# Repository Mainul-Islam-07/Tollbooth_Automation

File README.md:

#  🚧 Tollbooth_Automation
## ℹ️ Overview
Developed an automated tollbooth system capable of managing vehicle access efficiently, securely, and intelligently using a state machine–based control architecture.
The core logic is modeled as a finite state machine, enabling the system to transition between different operational modes depending on real-time triggers like camera input, payment status, vehicle movement, or override commands.
## 🌟 Highlights

### Microcontroller 💻
STM32F103C8t6 is used as the microcontroller.

### Ethernet Communication 🌐
Wiznet W5500 is used for Ethernet communication with the computer.

### UART Communication 🔄
Two UART communication interfaces (One of them is for debugging).

## ⚙️ Features 
### Vehicle Detection (Entry) 🚗
Detection of an approaching vehicle using inductive loop coils installed on the entry lane.

### Automated Boom Barrier Control 🚧
The boom barrier is raised or lowered based on toll payment status and vehicle position, ensuring only authorized passage.

### Vehicle Detection (Exit) 🚙
Detection of a car leaving the toll area is also handled via loop coils on the exit side.

### Car Exit Confirmation via IR Sensor 🌟
An IR sensor provides an additional check to confirm that the car has left the toll zone properly.

### Siren Control for Violations 🚨
A siren is triggered in case of illegal car passage (e.g., unpaid exit) and turned off after resolution or proper payment.

### TCU Breach Detection 🔒
The system monitors for unauthorized access or tampering with the Toll Controller Unit (TCU) and issues alerts on breach.

### Lane Operation Light Control 💡
The system manages lane indicator lights, guiding operators and drivers based on system state (e.g., red/green lights for status).

### Overhead Light Control 🌙
Overhead lighting at the booth is automatically controlled depending on operational mode or time of day.

### Additional Device Control (x3) ⚙️
Provision to control three additional AC or DC devices, configurable for future expansion (e.g., fan, display board, heater).

### PC Power Control (Upcoming) 💻
Planned feature to automatically turn the PC on/off based on toll activity or scheduled requirements. (Not yet implemented)

### Event Logging with External RTC (Upcoming) 🕰️
Future capability to log system events and state changes using a Real-Time Clock (RTC) module for time-stamped data. (Not yet implemented)

## Other Important aspects:

### Wiznet Interrupt-Based Communications 

### UART DMA Interrupt-Based Communication 

### Optocoupler-Based Input/Output for Isolation

### Encrypted Communication 🔐 (Not implemented yet)

## LED Board Config

## 🔁State Machine

## 🔧 Input/Output Circuit Diagram (Not Updated - Need Fix)

## PCB Sample Image

## Proteus Simulation Sample (Not Updated - Need Fix)

# ICPS Header Connection between PCBs

# Relay Board Pinout

## ⬇️ Installation

Download and Install STM32CubeIDE from https://www.st.com/en/development-tools/stm32cubeide.html

Download and Install Hercules from https://www.hw-group.com/software/hercules-setup-utility

Download and Install Serial Debugger Assistant from https://apps.microsoft.com/detail/9nblggh43hdm?hl=en-US&gl=US

## Setup

1) Download the zip or fork and then clone to a local directory
2) Import the folder as a project in STM32CubeIde
3) Plug the mcu using st-link v2 where,

| MCU Pin (90° Bent)     | Corresponding Pin on ST Link V2 |
|------------------------|-------------------|
| 3V3 (90 Degree Bent)   | 3V3               |
| GND (90 Degree Bent)   | GND               |
| SWDIO (90 Degree Bent) | SWDIO             |
| SCLK (90 Degree Bent)  | SCLK              |

Like this,

Then, plug the usb type A of ST-LINK V2 to Computer.

4) Press "Run" in the CubeIDE. Done!

# PCB PROBLEMS / SOLUTIONS / CONCERNS

2nd Iteration PCB is not finalized yet.

## TOLL CONTROLLER UNIT

1) SCLK And RST Connection from W5500 to MCU is manually swapped using wires. It should be fixed in next PCB design Iteration.
2) TX and RX connection from both UARTs is manually swapped using wires. The ususal way is UART TX > MCU TX and UART RX > MCU RX. To be fixed in the nextIteration.

3) Since less current flow at Input, 1k ohm resistors attached at all of the 4 inputs in replaced by wire (shorting). Now the optocoupler responses any voltage from 6V. To be fixed in next iteration.
4) Voltage divider resistors are changed from 22k and 33k to 470 and 1k ohm for all inputs. It provides proper input to the mcu pins. To be fixed in next iteration.

5) All 470 ohm connected from MCU to Relay signal input side is manually shorted. This is done for proper signal sending. To be fixed in next iteration.
6) Voltage divider resistors are changed from 22k and 33k to 33k and 100k for All UART RX. To be fixed in the next iteration.

8) w5500 needs to be powered using a regulator from 5V to 3.3V. To be Fixed in next iteration.

## RELAY BOARD

1) The resistor after 470 ohm should not be used. It should be kept open. To be fixed in the next iteration.
2) A pullup of 10k is given from 12 volt to base of bc557 in such a way that it can be made 0V / 12V when needed. To be fixed in the next iteration.

3) Pulldown resistor is given of 100k ohm resistors.

## LED BOARD

1) 1k ohm is connected to every signal end of mosfet used for powering RGB LED. Otherwise biasing issues emerge. To be fixed in the next iteration.

2) Led that are powered by mcu directly should be equiped with less value resistor, lets say 100ohm. Applicable for Camera_Trigger, Payment and Ping LEDs.

# CODE PROBLEMS / SOLUTIONS / CONCERNS

1) Individual Flags for sensor update should be implemented in next iteration. 
2) CMD_NO_COMMAND should replace CMD_RESET as default outcome from processcommand.

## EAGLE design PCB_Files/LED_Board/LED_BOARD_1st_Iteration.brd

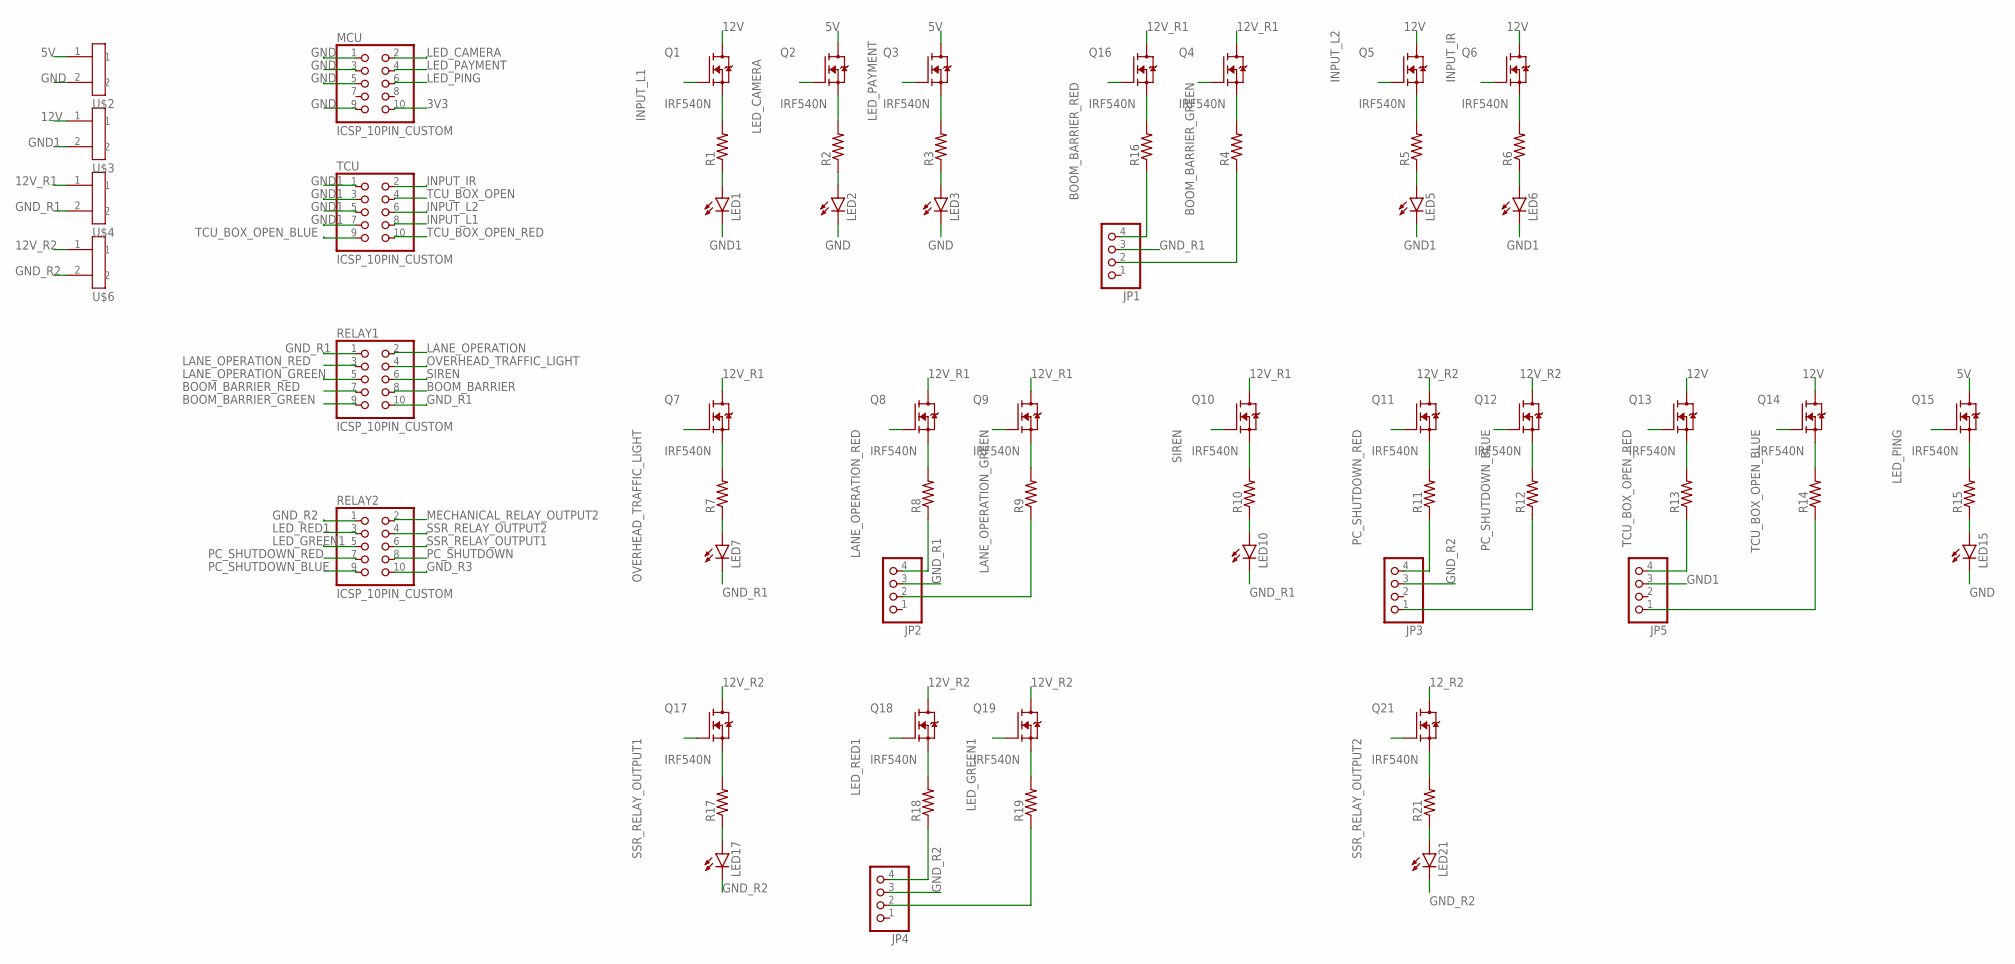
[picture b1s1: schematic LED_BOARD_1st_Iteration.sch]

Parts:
JP1, JP2, JP3, JP4, JP5: PINHD-1X4; 1X04
LED1, LED2, LED3, LED5, LED6, LED7, LED10, LED15, LED17, LED21: LED
MCU: ICSP_10PIN_CUSTOM
Q1, Q2, Q3, Q4, Q5, Q6, Q7, Q8, Q9, Q10, Q11, Q12, Q13, Q14, Q15, Q16, Q17, Q18, Q19, Q21: IRF540N; TO254P1054X469X1930-3
R1, R2, R3, R4, R5, R6, R7, R8, R9, R10, R11, R12, R13, R14, R15, R16, R17, R18, R19, R21: RESISTOR
RELAY1, RELAY2: ICSP_10PIN_CUSTOM
TCU: ICSP_10PIN_CUSTOM
U$2, U$3, U$4, U$6: GREEN_PLUG_90_2

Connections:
3V3: MCU.10
5V: Q2.2 (D), Q3.2 (D), Q15.2 (D), U$2.1
12V: Q1.2 (D), Q5.2 (D), Q6.2 (D), Q13.2 (D), Q14.2 (D), U$3.1
12V_R1: Q4.2 (D), Q7.2 (D), Q8.2 (D), Q9.2 (D), Q10.2 (D), Q16.2 (D), U$4.1
12V_R2: Q11.2 (D), Q12.2 (D), Q17.2 (D), Q18.2 (D), Q19.2 (D), U$6.1
12_R2: Q21.2 (D)
BOOM_BARRIER: RELAY1.8
BOOM_BARRIER_GREEN: Q4.1 (G), RELAY1.9
BOOM_BARRIER_RED: Q16.1 (G), RELAY1.7
GND: LED2.K (C), LED3.K (C), LED15.K (C), MCU.1, MCU.3, MCU.5, MCU.9, U$2.2
GND1: JP5.3, LED1.K (C), LED5.K (C), LED6.K (C), TCU.1, TCU.3, TCU.5, TCU.7, U$3.2
GND_R1: JP1.3, JP2.3, LED7.K (C), LED10.K (C), RELAY1.1, RELAY1.10, U$4.2
GND_R2: JP3.3, JP4.3, LED17.K (C), LED21.K (C), RELAY2.1, U$6.2
GND_R3: RELAY2.10
INPUT_IR: Q6.1 (G), TCU.2
INPUT_L1: Q1.1 (G), TCU.8
INPUT_L2: Q5.1 (G), TCU.6
LANE_OPERATION: RELAY1.2
LANE_OPERATION_GREEN: Q9.1 (G), RELAY1.5
LANE_OPERATION_RED: Q8.1 (G), RELAY1.3
LED_CAMERA: MCU.2, Q2.1 (G)
LED_GREEN1: Q19.1 (G), RELAY2.5
LED_PAYMENT: MCU.4, Q3.1 (G)
LED_PING: MCU.6, Q15.1 (G)
LED_RED1: Q18.1 (G), RELAY2.3
MECHANICAL_RELAY_OUTPUT2: RELAY2.2
unnamed: Q1.3 (S), R1.2
unnamed: LED1.A, R1.1
unnamed: JP1.4, R16.1
unnamed: JP1.2, R4.1
unnamed: JP2.4, R8.1
unnamed: Q2.3 (S), R2.2
unnamed: LED2.A, R2.1
unnamed: JP2.2, R9.1
unnamed: JP5.4, R13.1
unnamed: JP3.4, R11.1
unnamed: Q3.3 (S), R3.2
unnamed: LED3.A, R3.1
unnamed: JP3.1, R12.1
unnamed: JP5.1, R14.1
unnamed: Q4.3 (S), R4.2
unnamed: Q5.3 (S), R5.2
unnamed: LED5.A, R5.1
unnamed: Q6.3 (S), R6.2
unnamed: LED6.A, R6.1
unnamed: Q7.3 (S), R7.2
unnamed: LED7.A, R7.1
unnamed: Q8.3 (S), R8.2
unnamed: Q9.3 (S), R9.2
unnamed: Q10.3 (S), R10.2
unnamed: LED10.A, R10.1
unnamed: Q11.3 (S), R11.2
unnamed: Q12.3 (S), R12.2
unnamed: Q13.3 (S), R13.2
unnamed: Q14.3 (S), R14.2
unnamed: Q15.3 (S), R15.2
unnamed: LED15.A, R15.1
unnamed: Q16.3 (S), R16.2
unnamed: Q17.3 (S), R17.2
unnamed: LED17.A, R17.1
unnamed: Q18.3 (S), R18.2
unnamed: JP4.4, R18.1
unnamed: Q19.3 (S), R19.2
unnamed: JP4.2, R19.1
unnamed: Q21.3 (S), R21.2
unnamed: LED21.A, R21.1
OVERHEAD_TRAFFIC_LIGHT: Q7.1 (G), RELAY1.4
PC_SHUTDOWN: RELAY2.8
PC_SHUTDOWN_BLUE: Q12.1 (G), RELAY2.9
PC_SHUTDOWN_RED: Q11.1 (G), RELAY2.7
SIREN: Q10.1 (G), RELAY1.6
SSR_RELAY_OUTPUT1: Q17.1 (G), RELAY2.6
SSR_RELAY_OUTPUT2: Q21.1 (G), RELAY2.4
TCU_BOX_OPEN: TCU.4
TCU_BOX_OPEN_BLUE: Q14.1 (G), TCU.9
TCU_BOX_OPEN_RED: Q13.1 (G), TCU.10

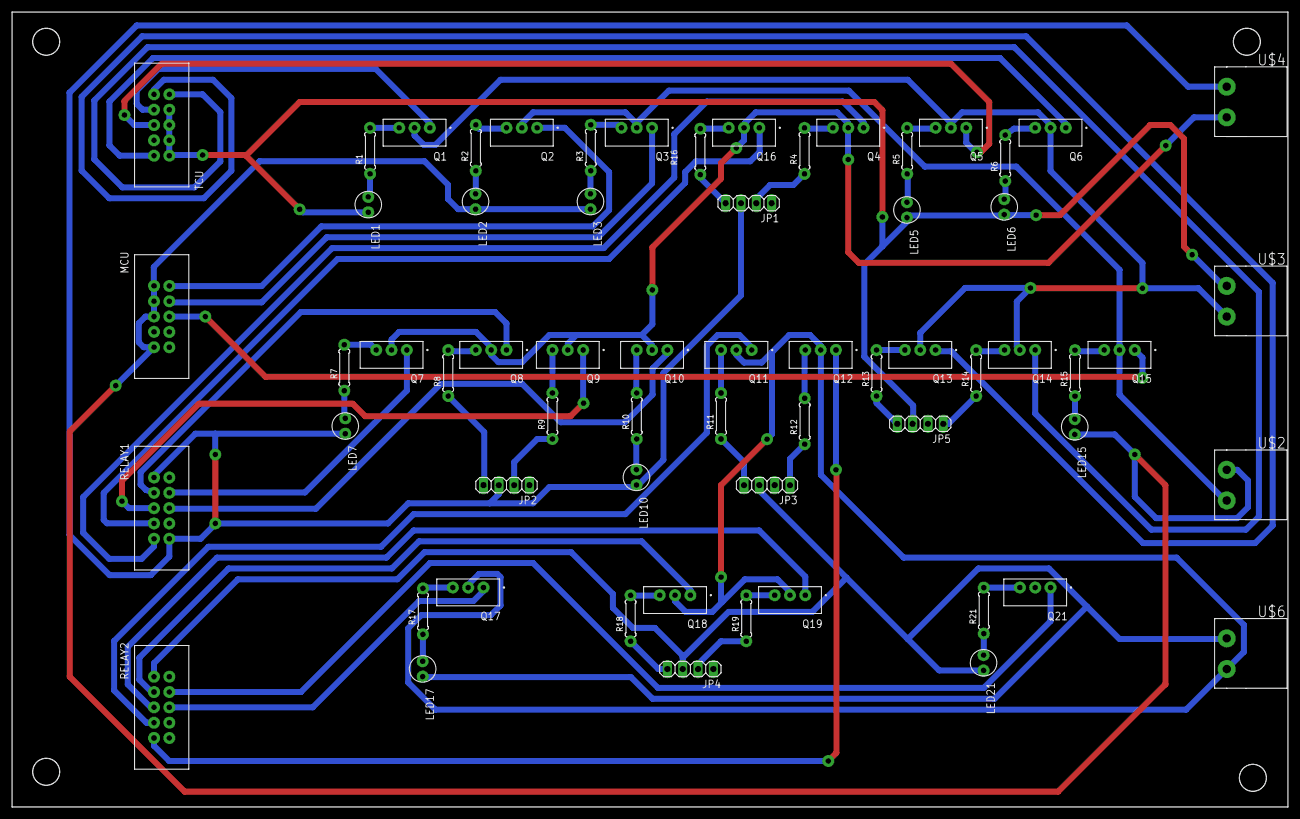
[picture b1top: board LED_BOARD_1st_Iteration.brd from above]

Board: 2 copper layers, 211.3 x 131.6 mm, 63 parts (0 on the bottom side), 68 nets.

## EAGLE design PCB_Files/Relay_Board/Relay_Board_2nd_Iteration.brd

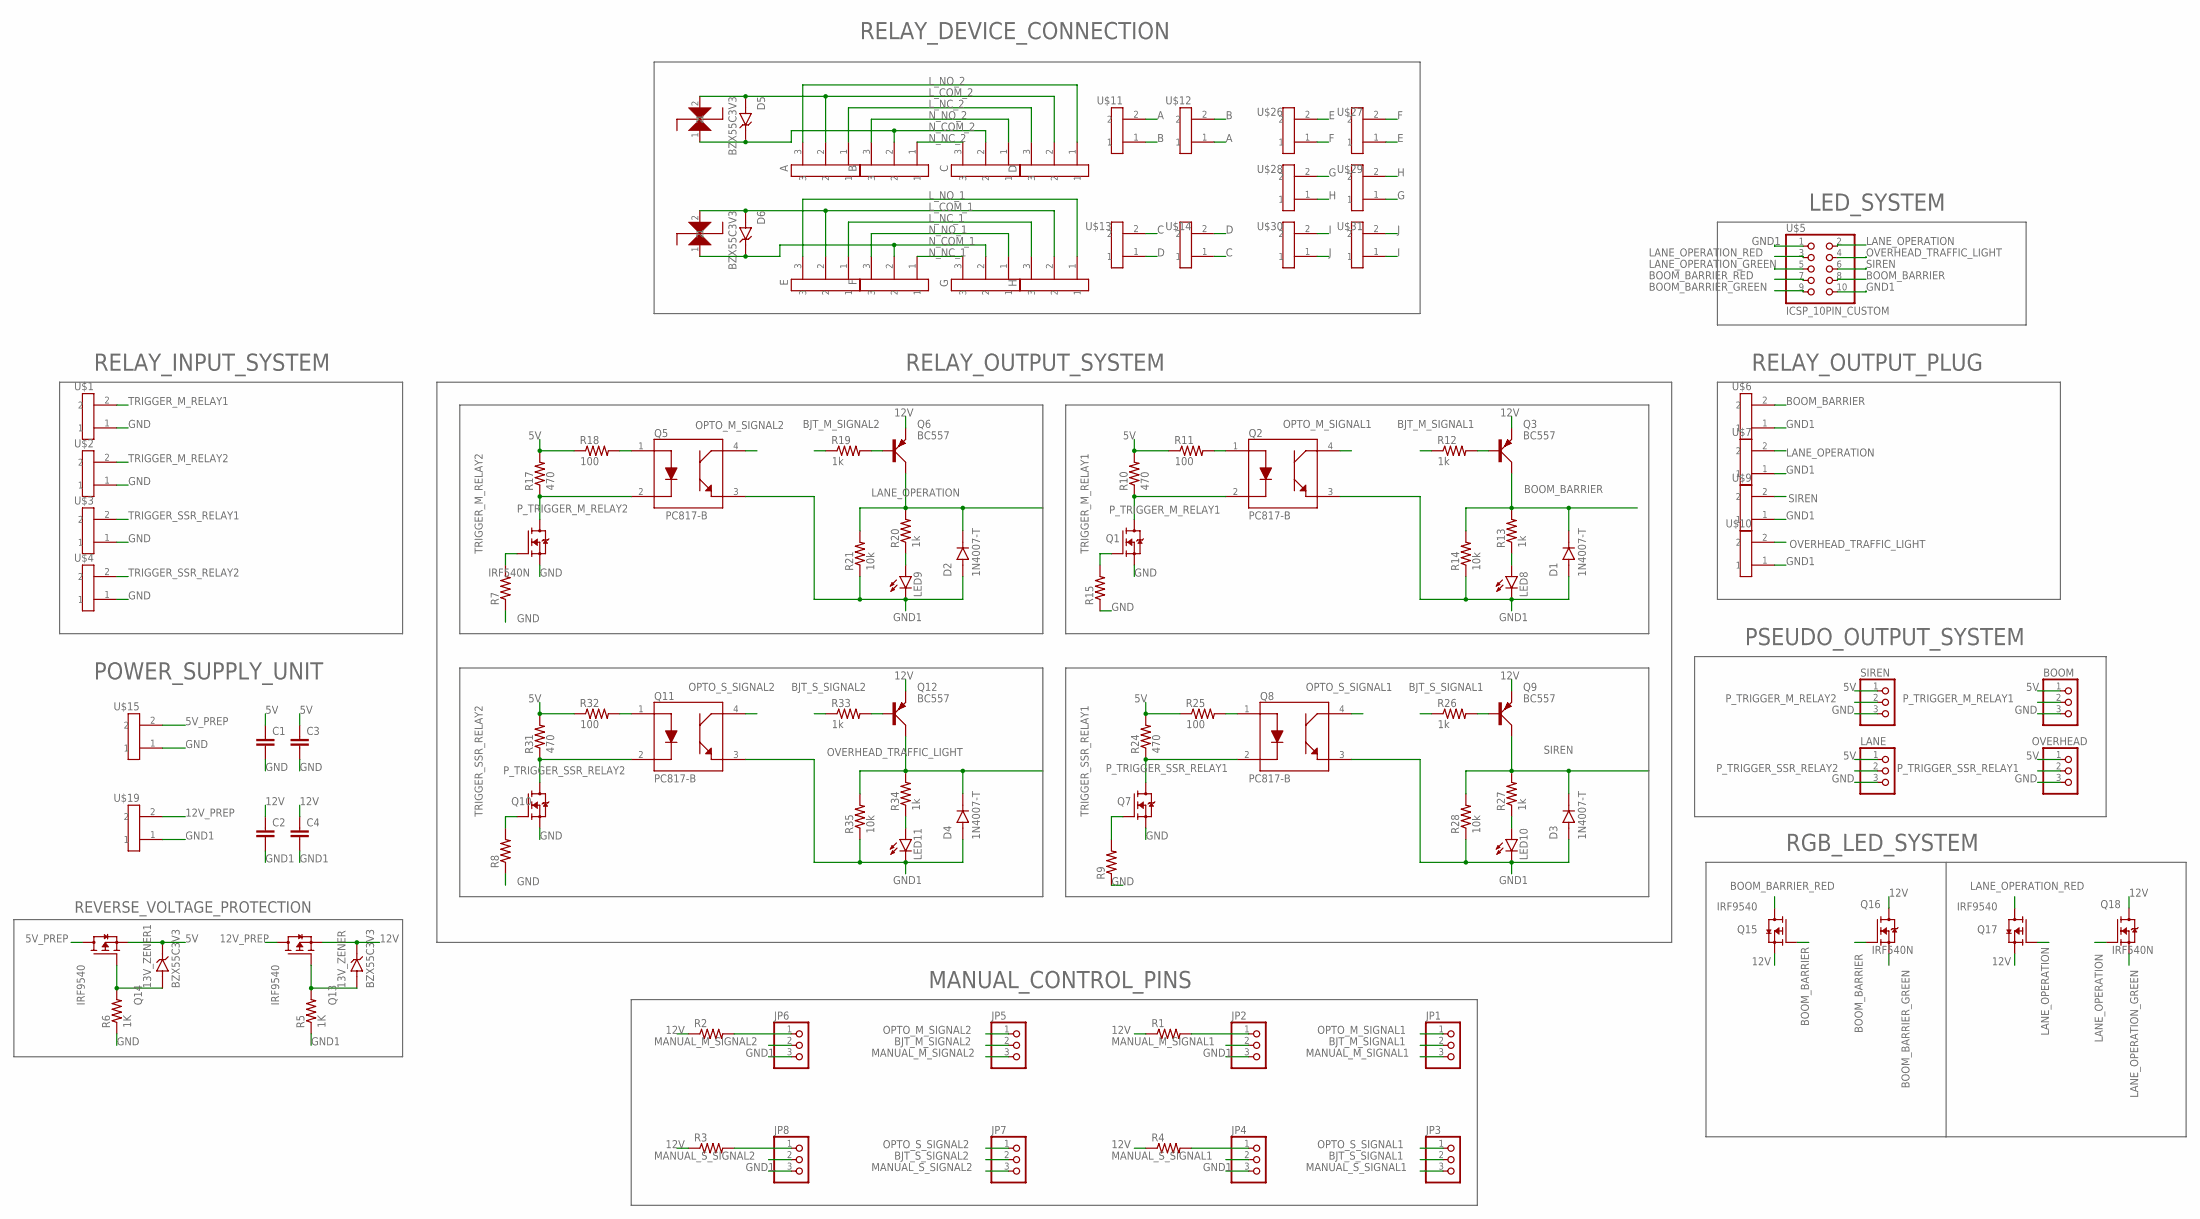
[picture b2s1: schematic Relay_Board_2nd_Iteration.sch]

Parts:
13V_ZENER, 13V_ZENER1: BZX55C3V3; DIOAD928W47L399D179
A: GREEN_PLUG_3
B: GREEN_PLUG_3
BOOM: PINHD-1X3; 1X03
C: GREEN_PLUG_90_3
C1, C2, C3, C4: CAPACITOR
D: GREEN_PLUG_90_3
D1, D2, D3, D4: 1N4007-T; DIOAD780W78L463D236
D5, D6: BZX55C3V3; DIOAD928W47L399D179
E: GREEN_PLUG_3
F: GREEN_PLUG_3
G: GREEN_PLUG_90_3
H: GREEN_PLUG_90_3
JP1, JP2, JP3, JP4, JP5, JP6, JP7, JP8: PINHD-1X3; 1X03
LANE: PINHD-1X3; 1X03
LED8, LED9, LED10, LED11: LED
OVERHEAD: PINHD-1X3; 1X03
Q1, Q4, Q7, Q10, Q16, Q18: IRF540N; TO254P1054X469X1930-3
Q2, Q5, Q8, Q11: PC817-B; DIP762W50P254L650H455Q4B
Q3, Q6, Q9, Q12: BC557; SOT54A
Q13, Q14, Q15, Q17: IRF9540; TO254P1052X465X1989-3
R1, R2, R3, R4, R7, R8, R9, R15: RESISTOR
R5, R6: 1K; RESISTOR
R10, R17, R24, R31: 470; RESISTOR
R11, R18, R25, R32: 100; RESISTOR
R12, R13, R19, R20, R26, R27, R33, R34: 1k; RESISTOR
R14, R21, R28, R35: 10k; RESISTOR
SIREN: PINHD-1X3; 1X03
U$1, U$2, U$3, U$4, U$12, U$13, U$15, U$19, U$27, U$29, U$31: GREEN_PLUG_90_2
U$5: ICSP_10PIN_CUSTOM
U$6, U$7, U$9, U$10, U$11, U$14, U$26, U$28, U$30: GREEN_PLUG_2
U$24, U$25: 1KE100A_CUSTOM

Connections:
5V: 13V_ZENER1.C (K), BOOM.1, C1.1, C3.1, LANE.1, OVERHEAD.1, Q14.3 (S), R10.2, R11.1, R17.2, R18.1, R24.2, R25.1, R31.2, R32.1, SIREN.1
5V_PREP: Q14.2 (D), U$15.2
12V: 13V_ZENER.C (K), C2.1, C4.1, Q3.E, Q6.E, Q9.E, Q12.E, Q13.3 (S), Q15.3 (S), Q16.2 (D), Q17.3 (S), Q18.2 (D), R1.1, R2.1, R3.1, R4.1
12V_PREP: Q13.2 (D), U$19.2
A: U$11.2, U$12.1
B: U$11.1, U$12.2
BJT_M_SIGNAL1: JP1.2, R12.1
BJT_M_SIGNAL2: JP5.2, R19.1
BJT_S_SIGNAL1: JP3.2, R26.1
BJT_S_SIGNAL2: JP7.2, R33.1
BOOM_BARRIER: D1.K, Q3.C, Q15.1 (G), Q16.1 (G), R13.2, R14.2, U$5.8, U$6.2
BOOM_BARRIER_GREEN: Q16.3 (S), U$5.9
BOOM_BARRIER_RED: Q15.2 (D), U$5.7
C: U$13.2, U$14.1
D: U$13.1, U$14.2
E: U$26.2, U$27.1
F: U$26.1, U$27.2
G: U$28.2, U$29.1
GND: BOOM.3, C1.2, C3.2, LANE.3, OVERHEAD.3, Q1.3 (S), Q4.3 (S), Q7.3 (S), Q10.3 (S), R6.1, R7.1, R8.1, R9.1, R15.1, SIREN.3, U$1.1, U$2.1, U$3.1, U$4.1, U$15.1
GND1: C2.2, C4.2, D1.A, D2.A, D3.A, D4.A, JP2.3, JP4.3, JP6.3, JP8.3, LED8.K (C), LED9.K (C), LED10.K (C), LED11.K (C), Q2.3 (EMITTER), Q5.3 (EMITTER), Q8.3 (EMITTER), Q11.3 (EMITTER), R5.1, R14.1, R21.1, R28.1, R35.1, U$5.1, U$5.10, U$6.1, U$7.1, U$9.1, U$10.1, U$19.1
H: U$28.1, U$29.2
I: U$30.2, U$31.1
J: U$30.1, U$31.2
LANE_OPERATION: D2.K, Q6.C, Q17.1 (G), Q18.1 (G), R20.2, R21.2, U$5.2, U$7.2
LANE_OPERATION_GREEN: Q18.3 (S), U$5.5
LANE_OPERATION_RED: Q17.2 (D), U$5.3
L_COM_1: D6.A, E.2, H.2, U$25.2
L_COM_2: A.2, D.2, D5.A, U$24.2
L_NC_1: E.1, H.3
L_NC_2: A.1, D.3
L_NO_1: E.3, H.1
L_NO_2: A.3, D.1
MANUAL_M_SIGNAL1: JP1.3, JP2.2
MANUAL_M_SIGNAL2: JP5.3, JP6.2
MANUAL_S_SIGNAL1: JP3.3, JP4.2
MANUAL_S_SIGNAL2: JP7.3, JP8.2
unnamed: 13V_ZENER1.A, Q14.1 (G), R6.2
unnamed: Q3.B, R12.2
unnamed: 13V_ZENER.A, Q13.1 (G), R5.2
unnamed: JP2.1, R1.2
unnamed: JP4.1, R4.2
unnamed: LED8.A, R13.1
unnamed: Q2.1 (ANODE), R11.2
unnamed: Q6.B, R19.2
unnamed: LED9.A, R20.1
unnamed: Q5.1 (ANODE), R18.2
unnamed: Q9.B, R26.2
unnamed: LED10.A, R27.1
unnamed: Q8.1 (ANODE), R25.2
unnamed: JP6.1, R2.2
unnamed: Q12.B, R33.2
unnamed: LED11.A, R34.1
unnamed: Q11.1 (ANODE), R32.2
unnamed: JP8.1, R3.2
N_COM_1: D6.C (K), F.2, G.2, U$25.1
N_COM_2: B.2, C.2, D5.C (K), U$24.1
N_NC_1: F.1, G.3
N_NC_2: B.1, C.3
N_NO_1: F.3, G.1
N_NO_2: B.3, C.1
OPTO_M_SIGNAL1: JP1.1, Q2.4 (COLLECTOR)
OPTO_M_SIGNAL2: JP5.1, Q5.4 (COLLECTOR)
OPTO_S_SIGNAL1: JP3.1, Q8.4 (COLLECTOR)
OPTO_S_SIGNAL2: JP7.1, Q11.4 (COLLECTOR)
OVERHEAD_TRAFFIC_LIGHT: D4.K, Q12.C, R34.2, R35.2, U$5.4, U$10.2
P_TRIGGER_M_RELAY1: BOOM.2, Q1.2 (D), Q2.2 (CATHODE), R10.1
P_TRIGGER_M_RELAY2: Q4.2 (D), Q5.2 (CATHODE), R17.1, SIREN.2
P_TRIGGER_SSR_RELAY1: OVERHEAD.2, Q7.2 (D), Q8.2 (CATHODE), R24.1
P_TRIGGER_SSR_RELAY2: LANE.2, Q10.2 (D), Q11.2 (CATHODE), R31.1
SIREN: D3.K, Q9.C, R27.2, R28.2, U$5.6, U$9.2
TRIGGER_M_RELAY1: Q1.1 (G), R15.2, U$1.2
TRIGGER_M_RELAY2: Q4.1 (G), R7.2, U$2.2
TRIGGER_SSR_RELAY1: Q7.1 (G), R9.2, U$3.2
TRIGGER_SSR_RELAY2: Q10.1 (G), R8.2, U$4.2

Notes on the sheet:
RELAY_OUTPUT_SYSTEM
RELAY_OUTPUT_PLUG
PSEUDO_OUTPUT_SYSTEM
RELAY_INPUT_SYSTEM
POWER_SUPPLY_UNIT
RELAY_DEVICE_CONNECTION
MANUAL_CONTROL_PINS
REVERSE_VOLTAGE_PROTECTION
RGB_LED_SYSTEM
LED_SYSTEM

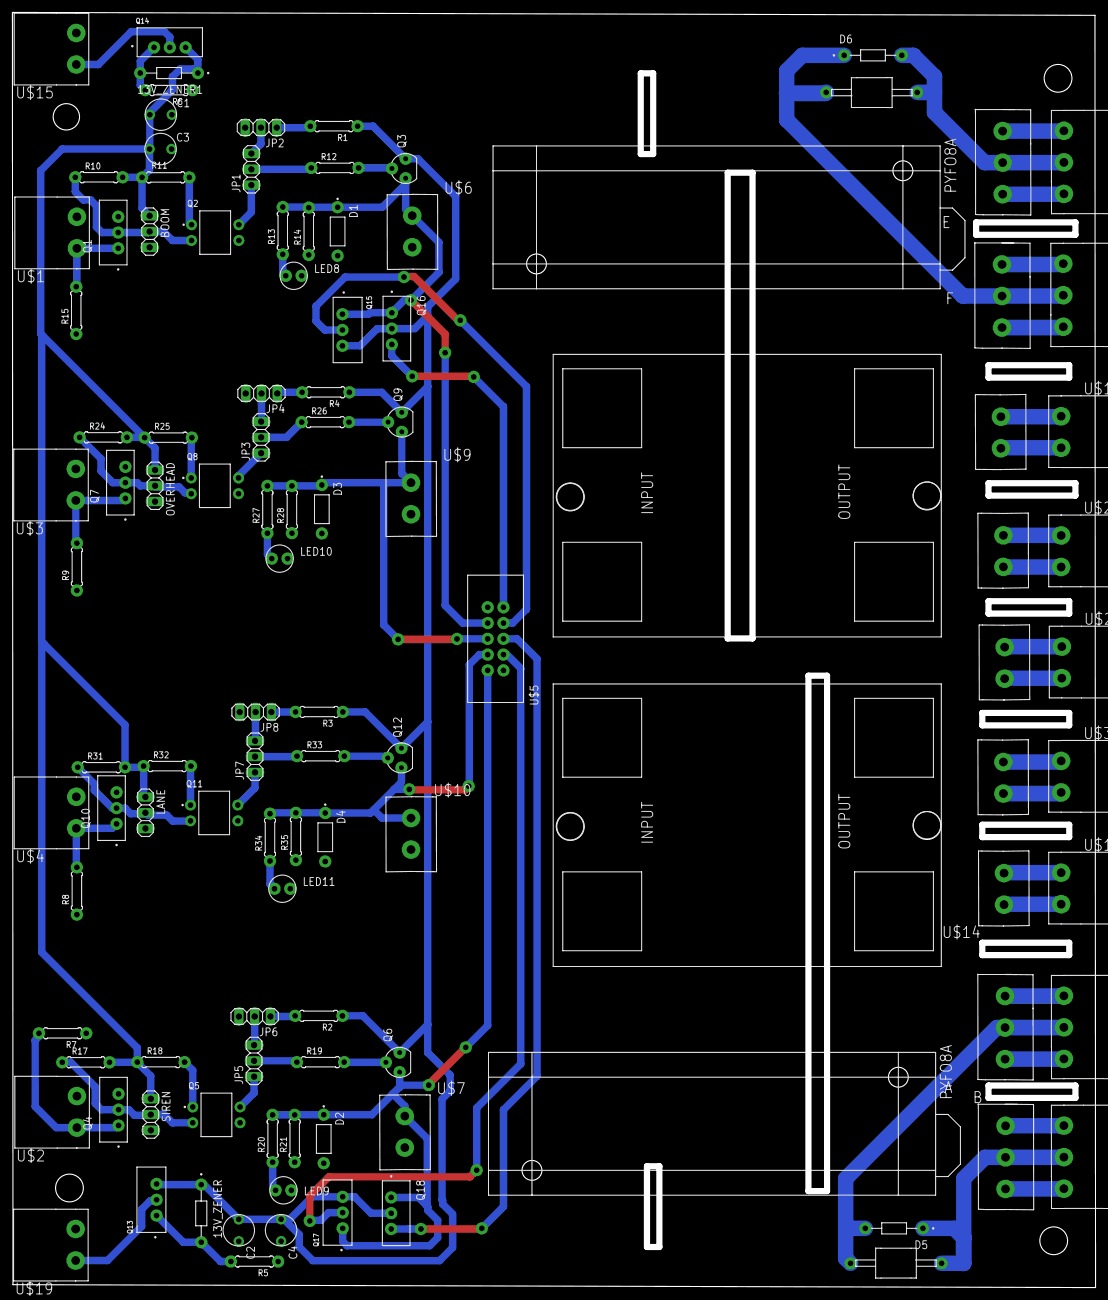
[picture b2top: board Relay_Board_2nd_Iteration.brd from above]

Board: 2 copper layers, 173.4 x 204.3 mm, 111 parts (0 on the bottom side), 74 nets.

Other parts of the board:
U$8, U$16: PYF08A-E
U$17, U$18: SSR-40DASOLIDSTATERELAYMODULE

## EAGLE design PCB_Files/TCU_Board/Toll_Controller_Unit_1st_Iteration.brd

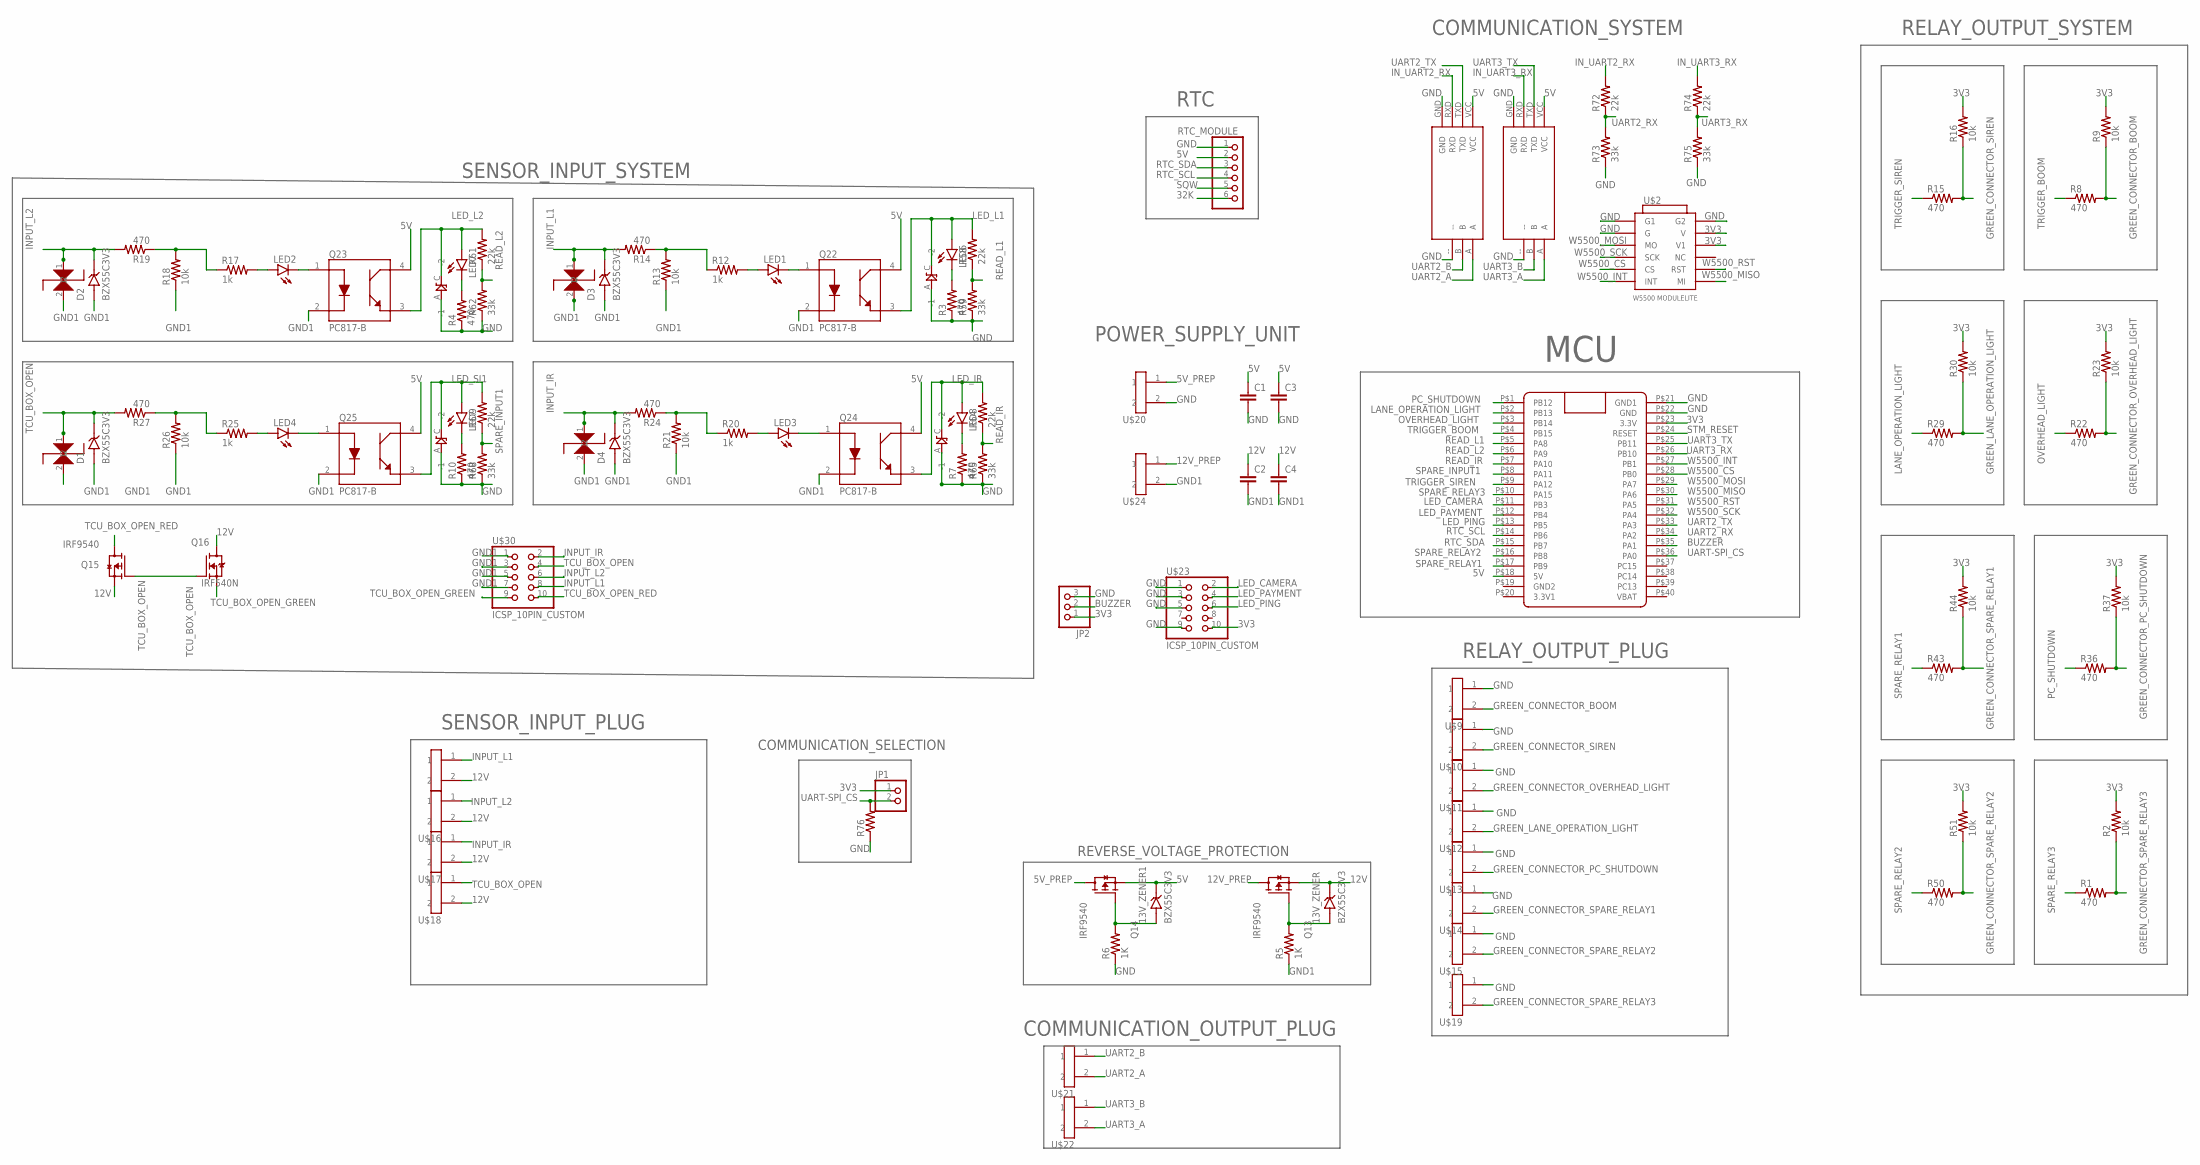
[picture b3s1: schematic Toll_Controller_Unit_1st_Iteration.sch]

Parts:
13V_ZENER, 13V_ZENER1: BZX55C3V3; DIOAD928W47L399D179
C1, C2, C3, C4: CAPACITOR
D1, D2, D3, D4: BZX55C3V3; DIOAD928W47L399D179
JP1: PINHD-1X2; 1X02
JP2: PINHD-1X3; 1X03
LED1, LED2, LED3, LED4, LED6, LED7, LED8, LED9: LED
Q13, Q14, Q15: IRF9540; TO254P1052X465X1989-3
Q16: IRF540N; TO254P1054X469X1930-3
Q22, Q23, Q24, Q25: PC817-B; DIP762W50P254L650H455Q4B
R1, R3, R4, R7, R8, R10, R14, R15, R19, R22, R24, R27, R29, R36, R43, R50: 470; RESISTOR
R2, R9, R13, R16, R18, R21, R23, R26, R30, R37, R44, R51: 10k; RESISTOR
R5, R6: 1K; RESISTOR
R12, R17, R20, R25: 1k; RESISTOR
R58, R61, R64, R67, R72, R74: 22k; RESISTOR
R59, R62, R65, R68, R73, R75: 33k; RESISTOR
R76: RESISTOR
RTC_MODULE: PINHD-1X6; 1X06
STM_BLUEPILL: BLUE_PILL
U$1, U$3, U$4, U$5: 1N227B
U$2: W5500_MODULELITE
U$6, U$9, U$10, U$11, U$12, U$13, U$14, U$15, U$16, U$17, U$18, U$19, U$20, U$21, U$22, U$24: GREEN_PLUG_90_2
U$7, U$8: RS485_CHINESE
U$23, U$30: ICSP_10PIN_CUSTOM
U$25, U$26, U$27, U$28: 1KE100A_CUSTOM

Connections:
3V3: JP1.1, JP2.1, R2.2, R9.2, R16.2, R23.2, R30.2, R37.2, R44.2, R51.2, STM_BLUEPILL.P$23 (3.3V), U$2.V, U$2.V1, U$23.10
5V: 13V_ZENER1.C (K), C1.1, C3.1, Q14.3 (S), Q22.4 (COLLECTOR), Q23.4 (COLLECTOR), Q24.4 (COLLECTOR), Q25.4 (COLLECTOR), RTC_MODULE.2, STM_BLUEPILL.P$18 (5V), U$7.VCC, U$8.VCC
5V_PREP: Q14.2 (D), U$20.1
12V: 13V_ZENER.C (K), C2.1, C4.1, Q13.3 (S), Q15.3 (S), Q16.2 (D), U$6.2, U$16.2, U$17.2, U$18.2
12V_PREP: Q13.2 (D), U$24.1
32K: RTC_MODULE.6
BUZZER: JP2.2, STM_BLUEPILL.P$35 (PA1)
GND: C1.2, C3.2, JP2.3, R3.1, R4.1, R6.1, R7.1, R10.1, R59.1, R62.1, R65.1, R68.1, R73.1, R75.1, R76.1, RTC_MODULE.1, STM_BLUEPILL.P$21 (GND1), STM_BLUEPILL.P$22 (GND), U$1.A (-1), U$2.G, U$2.G1, U$2.G2, U$3.A (-1), U$4.A (-1), U$5.A (-1), U$7.--, U$7.GND, U$8.--, U$8.GND, U$9.1, U$10.1, U$11.1, U$12.1, U$13.1, U$14.1, U$15.1, U$19.1, U$20.2, U$23.1, U$23.3, U$23.5, U$23.9
GND1: C2.2, C4.2, D1.A, D2.A, D3.A, D4.A, Q22.2 (CATHODE), Q23.2 (CATHODE), Q24.2 (CATHODE), Q25.2 (CATHODE), R5.1, R13.1, R18.1, R21.1, R26.1, U$24.2, U$25.2, U$26.2, U$30.1, U$30.3, U$30.5, U$30.7
GREEN_CONNECTOR_BOOM: R8.2, R9.1, U$9.2
GREEN_CONNECTOR_OVERHEAD_LIGHT: R22.2, R23.1, U$11.2
GREEN_CONNECTOR_PC_SHUTDOWN: R36.2, R37.1, U$13.2
GREEN_CONNECTOR_SIREN: R15.2, R16.1, U$10.2
GREEN_CONNECTOR_SPARE_RELAY1: R43.2, R44.1, U$14.2
GREEN_CONNECTOR_SPARE_RELAY2: R50.2, R51.1, U$15.2
GREEN_CONNECTOR_SPARE_RELAY3: R1.2, R2.1, U$19.2
GREEN_LANE_OPERATION_LIGHT: R29.2, R30.1, U$12.2
INPUT_IR: D4.C (K), R24.2, U$17.1, U$27.1, U$30.2
INPUT_L1: D3.C (K), R14.2, U$6.1, U$25.1, U$30.8
INPUT_L2: D2.C (K), R19.2, U$16.1, U$28.1, U$30.6
IN_UART2_RX: R72.2, U$8.RXD
IN_UART3_RX: R74.2, U$7.RXD
LANE_OPERATION_LIGHT: R29.1, STM_BLUEPILL.P$2 (PB13)
LED_CAMERA: STM_BLUEPILL.P$11 (PB3), U$23.2
LED_IR: LED8.A, Q24.3 (EMITTER), R64.2, U$4.C (-2)
LED_L1: LED6.A, Q22.3 (EMITTER), R58.2, U$1.C (-2)
LED_L2: LED7.A, Q23.3 (EMITTER), R61.2, U$3.C (-2)
LED_PAYMENT: STM_BLUEPILL.P$12 (PB4), U$23.4
LED_PING: STM_BLUEPILL.P$13 (PB5), U$23.6
LED_SI1: LED9.A, Q25.3 (EMITTER), R67.2, U$5.C (-2)
unnamed: 13V_ZENER1.A, Q14.1 (G), R6.2
unnamed: 13V_ZENER.A, Q13.1 (G), R5.2
unnamed: LED6.K (C), R3.2
unnamed: LED7.K (C), R4.2
unnamed: LED8.K (C), R7.2
unnamed: LED9.K (C), R10.2
unnamed: LED1.A, R12.2
unnamed: R12.1, R13.2, R14.1
unnamed: LED2.A, R17.2
unnamed: R17.1, R18.2, R19.1
unnamed: LED3.A, R20.2
unnamed: R20.1, R21.2, R24.1
unnamed: R25.1, R26.2, R27.1
unnamed: LED4.A, R25.2
unnamed: LED1.K (C), Q22.1 (ANODE)
unnamed: LED3.K (C), Q24.1 (ANODE)
unnamed: LED4.K (C), Q25.1 (ANODE)
unnamed: LED2.K (C), Q23.1 (ANODE)
OVERHEAD_LIGHT: R22.1, STM_BLUEPILL.P$3 (PB14)
PC_SHUTDOWN: R36.1, STM_BLUEPILL.P$1 (PB12)
READ_IR: R64.1, R65.2, STM_BLUEPILL.P$7 (PA10)
READ_L1: R58.1, R59.2, STM_BLUEPILL.P$5 (PA8)
READ_L2: R61.1, R62.2, STM_BLUEPILL.P$6 (PA9)
RTC_SCL: RTC_MODULE.4, STM_BLUEPILL.P$14 (PB6)
RTC_SDA: RTC_MODULE.3, STM_BLUEPILL.P$15 (PB7)
SPARE_INPUT1: R67.1, R68.2, STM_BLUEPILL.P$8 (PA11)
SPARE_RELAY1: R43.1, STM_BLUEPILL.P$17 (PB9)
SPARE_RELAY2: R50.1, STM_BLUEPILL.P$16 (PB8)
SPARE_RELAY3: R1.1, STM_BLUEPILL.P$10 (PA15)
SQW: RTC_MODULE.5
STM_RESET: STM_BLUEPILL.P$24 (RESET)
TCU_BOX_OPEN: D1.C (K), Q15.1 (G), Q16.1 (G), R27.2, U$18.1, U$26.1, U$30.4
TCU_BOX_OPEN_GREEN: Q16.3 (S), U$30.9
TCU_BOX_OPEN_RED: Q15.2 (D), U$30.10
TRIGGER_BOOM: R8.1, STM_BLUEPILL.P$4 (PB15)
TRIGGER_SIREN: R15.1, STM_BLUEPILL.P$9 (PA12)
UART2_A: U$8.A, U$21.2
UART2_B: U$8.B, U$21.1
UART2_RX: R72.1, R73.2, STM_BLUEPILL.P$34 (PA2)
UART2_TX: STM_BLUEPILL.P$33 (PA3), U$8.TXD
UART3_A: U$7.A, U$22.2
UART3_B: U$7.B, U$22.1
UART3_RX: R74.1, R75.2, STM_BLUEPILL.P$26 (PB10)
UART3_TX: STM_BLUEPILL.P$25 (PB11), U$7.TXD
UART-SPI_CS: JP1.2, R76.2, STM_BLUEPILL.P$36 (PA0)
W5500_CS: STM_BLUEPILL.P$28 (PB0), U$2.CS
W5500_INT: STM_BLUEPILL.P$27 (PB1), U$2.INT
W5500_MISO: STM_BLUEPILL.P$30 (PA6), U$2.MI
W5500_MOSI: STM_BLUEPILL.P$29 (PA7), U$2.MO
W5500_RST: STM_BLUEPILL.P$31 (PA5), U$2.RST
W5500_SCK: STM_BLUEPILL.P$32 (PA4), U$2.SCK

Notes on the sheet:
MCU
COMMUNICATION_SYSTEM
POWER_SUPPLY_UNIT
SENSOR_INPUT_SYSTEM
RELAY_OUTPUT_SYSTEM
RELAY_OUTPUT_PLUG
SENSOR_INPUT_PLUG
RTC
COMMUNICATION_OUTPUT_PLUG
COMMUNICATION_SELECTION
REVERSE_VOLTAGE_PROTECTION

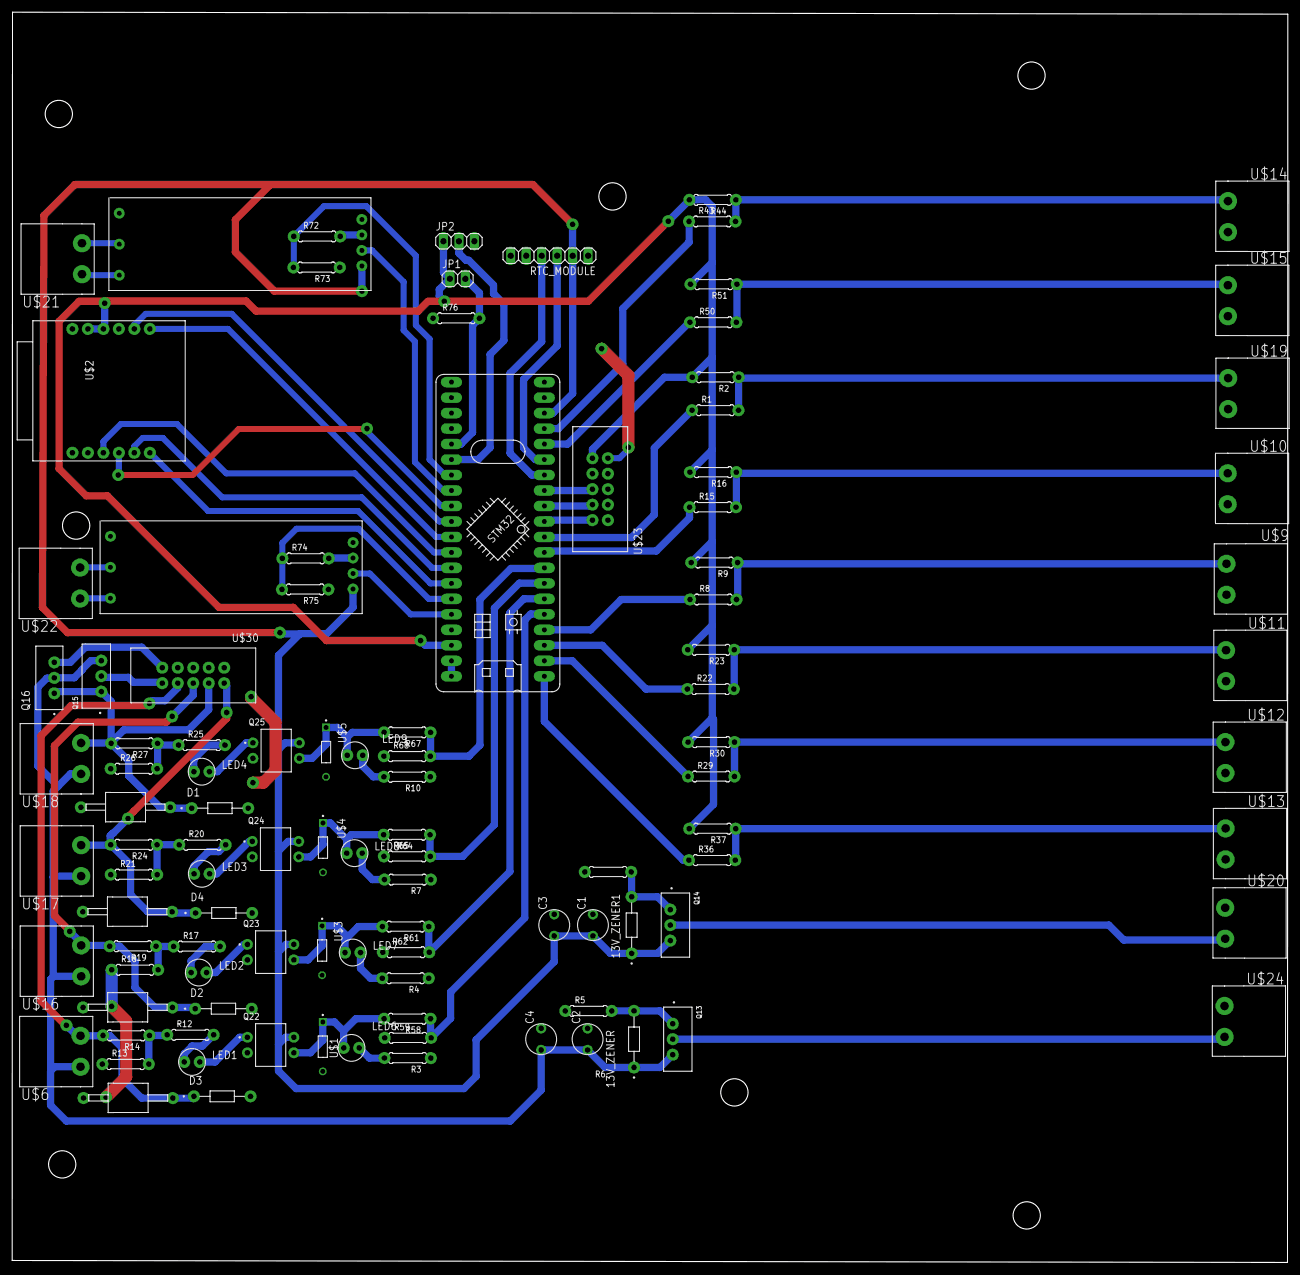
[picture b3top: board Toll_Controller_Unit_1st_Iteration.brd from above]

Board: 2 copper layers, 209.1 x 205.0 mm, 106 parts (0 on the bottom side), 78 nets.

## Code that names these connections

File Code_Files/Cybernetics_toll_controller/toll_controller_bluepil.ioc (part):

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Mcu.Name=STM32F103C(8-B)Tx
Mcu.Package=LQFP48
Mcu.UserName=STM32F103C8Tx
PA10.GPIOParameters=GPIO_PuPd,GPIO_Label,GPIO_ModeDefaultEXTI
PA10.GPIO_Label=IR_INPUT
PA10.GPIO_ModeDefaultEXTI=GPIO_MODE_IT_RISING_FALLING
PA10.GPIO_PuPd=GPIO_PULLDOWN
PA10.Signal=GPXTI10
PA11.GPIOParameters=GPIO_PuPd,GPIO_Label,GPIO_ModeDefaultEXTI
PA11.GPIO_Label=TCU_BOX_STATUS
PA11.GPIO_ModeDefaultEXTI=GPIO_MODE_IT_RISING_FALLING
PA11.GPIO_PuPd=GPIO_PULLDOWN
PA11.Signal=GPXTI11
PA12.GPIOParameters=GPIO_Label
PA12.GPIO_Label=SIREN
PA12.Signal=GPIO_Output
PA13.Mode=Serial_Wire
PA13.Signal=SYS_JTMS-SWDIO
PA14.Mode=Serial_Wire
PA14.Signal=SYS_JTCK-SWCLK
PA2.Mode=Asynchronous
PA2.Signal=USART2_TX
PA3.Mode=Asynchronous
PA3.Signal=USART2_RX
PA4.GPIOParameters=GPIO_Label
PA4.GPIO_Label=W5500_RESET
PA4.Signal=GPIO_Output
PA5.Mode=Full_Duplex_Master
PA5.Signal=SPI1_SCK
PA6.Mode=Full_Duplex_Master
PA6.Signal=SPI1_MISO
PA7.Mode=Full_Duplex_Master
PA7.Signal=SPI1_MOSI
PA8.GPIOParameters=GPIO_PuPd,GPIO_Label,GPIO_ModeDefaultEXTI
PA8.GPIO_Label=ENTRYLOOP_COIL
PA8.GPIO_ModeDefaultEXTI=GPIO_MODE_IT_RISING_FALLING
PA8.GPIO_PuPd=GPIO_PULLDOWN
PA8.Signal=GPXTI8
PA9.GPIOParameters=GPIO_PuPd,GPIO_Label,GPIO_ModeDefaultEXTI
PA9.GPIO_Label=EXITLOOP_COIL
PA9.GPIO_ModeDefaultEXTI=GPIO_MODE_IT_RISING_FALLING
PA9.GPIO_PuPd=GPIO_NOPULL
PA9.Signal=GPXTI9
PB0.GPIOParameters=GPIO_Label
PB0.GPIO_Label=W5500_CS
PB0.Signal=GPIO_Output
PB1.GPIOParameters=GPIO_PuPd,GPIO_Label,GPIO_ModeDefaultEXTI
PB1.GPIO_Label=W5500_INT
PB1.GPIO_ModeDefaultEXTI=GPIO_MODE_IT_FALLING
PB1.GPIO_PuPd=GPIO_PULLUP
PB1.Signal=GPXTI1
PB10.Mode=Asynchronous
PB10.Signal=USART3_TX
PB11.Mode=Asynchronous
PB11.Signal=USART3_RX
PB12.GPIOParameters=GPIO_Label
PB12.GPIO_Label=POWER
PB12.Signal=GPIO_Output
PB13.GPIOParameters=GPIO_Label
PB13.GPIO_Label=LANE_OPERATION
PB13.Signal=GPIO_Output
PB14.GPIOParameters=GPIO_Label
PB14.GPIO_Label=OVERHEAD_LIGHT
PB14.Signal=GPIO_Output
PB15.GPIOParameters=GPIO_Label
PB15.GPIO_Label=BOOM_BARRIER
PB15.Signal=GPIO_Output
PB3.GPIOParameters=GPIO_PuPd,GPIO_Label
PB3.GPIO_Label=LED_CAMERA
PB3.GPIO_PuPd=GPIO_PULLDOWN
PB3.Signal=GPIO_Output
PB4.GPIOParameters=GPIO_PuPd,GPIO_Label
PB4.GPIO_Label=LED_PAYMENT
PB4.GPIO_PuPd=GPIO_PULLDOWN
PB4.Signal=GPIO_Output
PB5.GPIOParameters=GPIO_PuPd,GPIO_Label
PB5.GPIO_Label=LED_PING
PB5.GPIO_PuPd=GPIO_PULLDOWN
PB5.Signal=GPIO_Output
PB6.Mode=I2C
PB6.Signal=I2C1_SCL
PB7.Mode=I2C
PB7.Signal=I2C1_SDA
PC13-TAMPER-RTC.GPIOParameters=GPIO_Label
PC13-TAMPER-RTC.GPIO_Label=LD2
PC13-TAMPER-RTC.Signal=GPIO_Output
PD0-OSC_IN.Mode=HSE-External-Oscillator
PD0-OSC_IN.Signal=RCC_OSC_IN
PD1-OSC_OUT.Mode=HSE-External-Oscillator
PD1-OSC_OUT.Signal=RCC_OSC_OUT
RCC.SYSCLKFreq_VALUE=72000000
RCC.SYSCLKSource=RCC_SYSCLKSOURCE_PLLCLK
board=custom

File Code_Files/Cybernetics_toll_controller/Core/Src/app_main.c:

/*
 * app_main.c
 *
 *  Created on: Mar 9, 2025
 *      Author: User
 */

#include "app_main.h"
#include "tcp_handler.h"



GlobalParam global;
Event_t event;

//uint32_t error;
W5500_GPIO_Config_t w5500_config = {
      .cs_port = W5500_CS_GPIO_Port,         // Replace with your CS GPIO port
      .cs_pin = W5500_CS_Pin,    // Replace with your CS GPIO pin
      .reset_port = W5500_RESET_GPIO_Port,      // Replace with your Reset GPIO port
      .reset_pin = W5500_RESET_Pin, // Replace with your Reset GPIO pin
      .int_port = W5500_INT_GPIO_Port,        // Replace with your Interrupt GPIO port
      .int_pin = W5500_INT_Pin,   // Replace with your Interrupt GPIO pin
      .spi_handle = &hspi1      // Replace with your SPI handle
  };


  wiz_NetInfo netInfo = {
      .mac = { 0x00, 0x08, 0xdc, 0xab, 0xcd, 0xef },
      .ip = { 192, 168, 20, 14 },
      .sn = { 255, 255, 255, 0 },
      .gw = { 192, 168, 20, 1 },
      .dns = { 8, 8, 8, 8 },
      .dhcp = NETINFO_STATIC
  };


void init(void){
	global.debug_uart 	 = &huart3;
	global.comm_uart  	 = &huart2;

//	global.loop1.port 	 = LOOP_COIL_1_GPIO_Port;
//	global.loop2.port 	 = LOOP_COIL_2_GPIO_Port;
//	global.ir.port 	  	 = IR_INPUT_GPIO_Port;
//	global.boom.port  	 = BOOM_BARRIER_GPIO_Port;
//	global.siren.port    = SIREN_GPIO_Port;
//
//	global.ledLoop1.port = LED_L1_GPIO_Port;
//	global.ledLoop2.port = LED_L2_GPIO_Port;
//	global.ledIr.port    = LED_IR_GPIO_Port;
//	global.ledBoom.port  = LED_BOOM_GPIO_Port;
//	global.ledSiren.port = LED_SIREN_GPIO_Port;
//
//	global.loop1.pin  	 = LOOP_COIL_1_Pin;
//	global.loop2.pin     = LOOP_COIL_2_Pin;
//	global.ir.pin 	     = IR_INPUT_Pin;
//	global.boom.pin      = BOOM_BARRIER_Pin;
//	global.siren.pin     = SIREN_Pin;
//
//	global.ledLoop1.pin  = LED_L1_Pin;
//	global.ledLoop2.pin  = LED_L2_Pin;
//	global.ledIr.pin	 = LED_IR_Pin;
//	global.ledBoom.pin   = LED_BOOM_Pin;
//	global.ledSiren.pin  = LED_SIREN_Pin;
//
//	global.gpioWrite = gpioWrite;
//
//	global.gpioRead = gpioRead;
	  HAL_Delay(500);
      Trigger_Control(TRIGGER_POWER, ON);
	  HAL_Delay(1000);
	  startUartDMA(global.comm_uart);



	  //Initialize Wiznet w5500 with GPIOs, SPI and NetInfo
	  W5500Init(&w5500_config,&netInfo);


	  W5500_Init_Sockets();
	  rtcInit();

}


void loop(void){


	W5500_Handle_Events();
    event = generate_event(&sensorSystem, currentCommand, currentState);
    check_and_execute(currentCommand, currentState);
    currentCommand = CMD_NOCOMMAND;
    updatePrevSensorState(&sensorSystem);
    run_state_machine(&currentState, event);
    state_Trigger(currentState);
    rtcDatafetch();
    connectionFeedback();

    //check_phy_status();
//    checkerror();

   // error = HAL_UART_GetError(&huart2);

   // global.gpioWrite(&global.loop1, SET);


}

//void gpioWrite(GPIOConfig_t *gpio, GPIO_PinState state) {
//    HAL_GPIO_WritePin(gpio->port, gpio->pin, state);
//}
//
//uint8_t gpioRead(GPIOConfig_t *gpio) {
//    return
//    HAL_GPIO_ReadPin(gpio->port, gpio->pin);
//}
